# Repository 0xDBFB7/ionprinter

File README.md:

```
    _                       __        _  __   __  
   (_)____   ____   ____   / /____   (_)/ /_ / /_ 
  / // __ \ / __ \ / __ \ / // __ \ / // __// __ \
 / // /_/ // / / // /_/ // // /_/ // // /_ / / / /
/_/ \____//_/ /_/ \____//_/ \____//_/ \__//_/ /_/ 
```                                        

# Ionolith

Hardware, firmware, software, and documentation for ion printers.

This was an extremely speculative (and arguably pseudoscientific) project to attempt to scale up physical vapor deposition beyond all reasonable limits. I got as far as building a high vacuum chamber, testing a few "bowtie" crucible designs, etc.

Spinoffs:

- a GPU-accelerated Particle-In-Cell program called [Nyion](https://github.com/0xDBFB7/Nyion) 
- A cheap silicon carbide [furnace](https://0xdbfb7.com/furnace.html)
- A cheap controller for Varian Turbo-V200 series of pumps [varian-turbo-controller](https://github.com/0xDBFB7/varian-turbo-controller)
- Control software for an Inficon BPG-400 vacuum gauge [gauge.py](https://gist.github.com/0xDBFB7/7bd7048c6639270e6f291a2673903184)

This whole project was far beyond my capabilities, suffers from a lack of basic physical modelling in the beam region, and so there is little basis to expect this to work.

At the time the project was suspended, it looked something like this:

The ultimate goal was to produce an ultra high current (somewhere around 100 A of ionized aluminum accelerated to 100 to 1000 eV) heavy ion beam deposition system, aiming to 3D print large parts at cubic centimeters per hour and with arbitrary combinations of alloys and crystalline structure. 

  - Heavy ions like Al move slowly, meaning space charge effects are huge and, due to so-called "beam rigidity", magnetic focusing is useless.
  - However, this was developed under the (as yet untested assumption) that it would be possible to use a sort of active space-charge neutralization, actively injecting and confining electrons into metal-ion "packets" in the beam, to neutralize the beam space charge (something like [Gotoh 2012]).
  - Spreading the beam current over 512 or 1024 individually-controlled emitters in a 0.25 m^2 area seemed like it might alleviate deposition surface roughness issues, because of the wide range of angles of incidence.(See [Yang and Zhou, 1999, 2001])
  - Feedstock would be vaporized in "bowtie" structure - perhaps graphite-loaded magnesium oxide, perhaps coated in aluminum nitride, and with layers of ceramic multi-layer insulation to mitigate heat loss. Basic testing on a graphite bowtie was done.
  - Design goal of <$2000 cost, ideally run from a single 1500w outlet, with integrated diffusion pump.
  - Acceleration voltages over ~5000 V would pose huge X-ray and general power consumption (dozens of kilowatts in the beam!) and deposition power density (build platform overheating) issues.

```
Gotoh Y, Tsuji H, Taguchi S, Ikeda K, Kitagawa T, Ishikawa J, et al. Neutralization of space charge on high-current low-energy ion beam by low-energy electrons supplied from silicon based field emitter arrays. AIP Conference Proceedings, vol. 1496, 2012, p. 368–71.
Zhou XW, Wadley HNG. Hyperthermal vapor deposition of copper: reflection and resputtering effects. Surface Science 1999;431:58–73. https://doi.org/10.1016/S0039-6028(99)00336-2.
Yang YG, Zhou XW, Johnson RA, Wadley HNG. Monte Carlo simulation of hyperthermal physical vapor deposition. Acta Materialia 2001;49:3321–32. https://doi.org/10.1016/S1359-6454(01)00139-2.
```

For all references involved, see the file references.bib.

# <3     

# :D

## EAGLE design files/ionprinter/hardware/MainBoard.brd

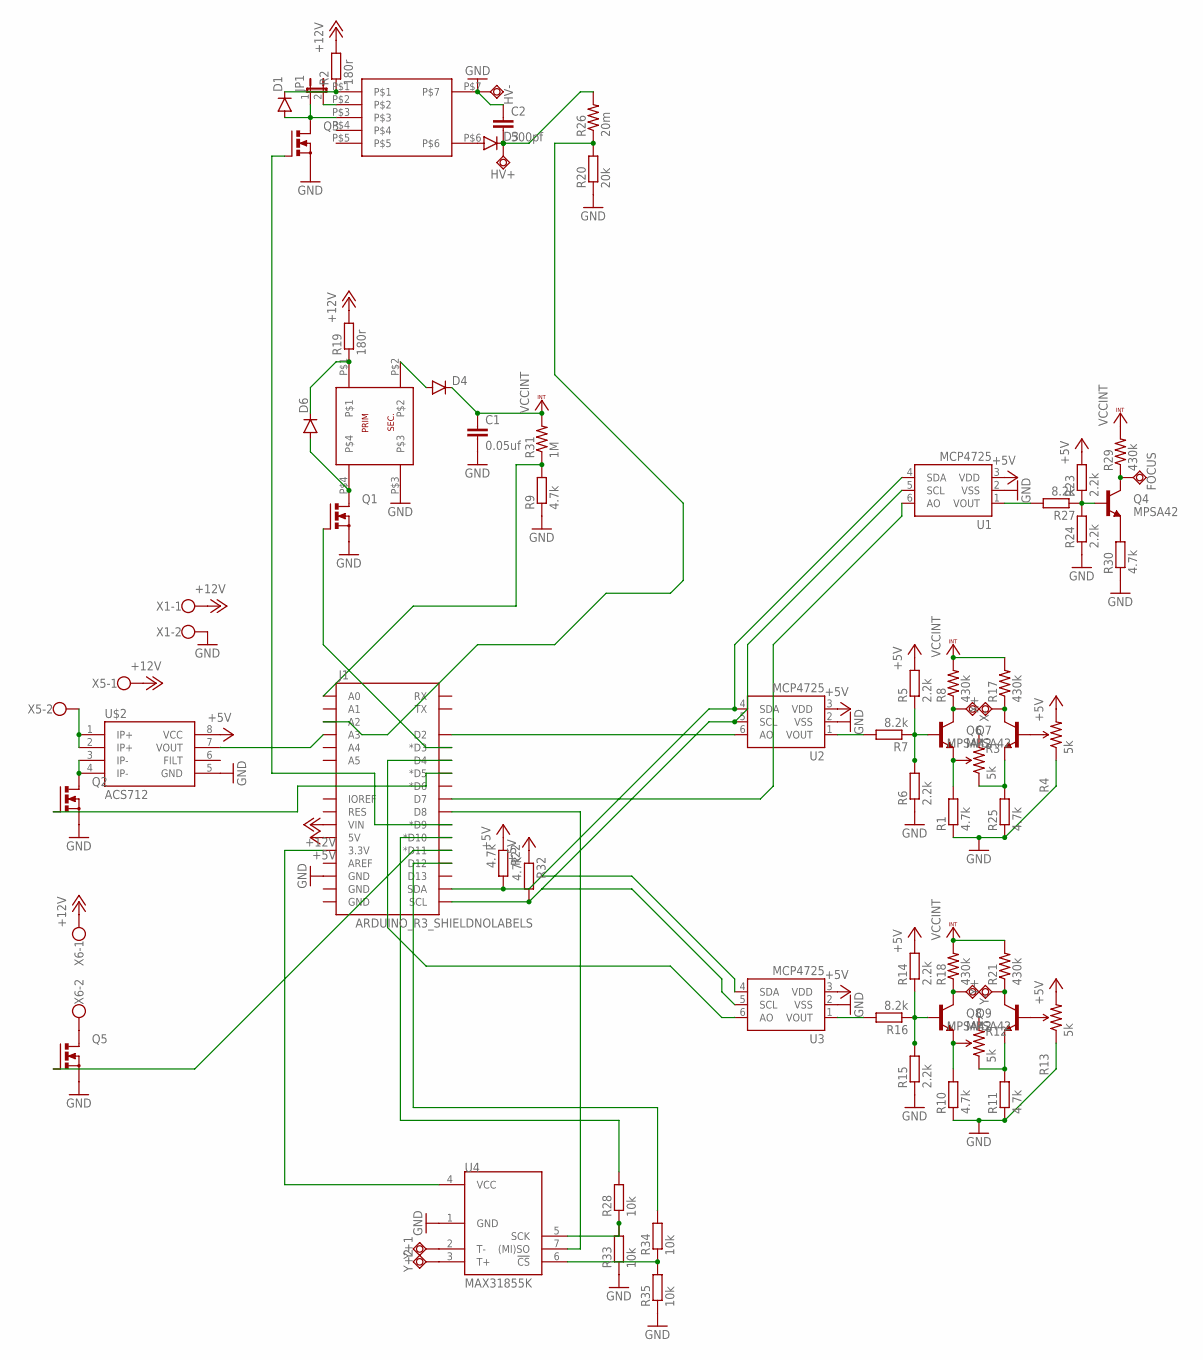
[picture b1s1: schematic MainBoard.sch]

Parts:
C1: 0.05uf; C1206
C2: 500pf; C1206
D1, D4, D6: DIODESOD123; SOD-123
D3: DIODEPTH; DIODE-1N4001
FOCUS: FOCUS; P1-13
HV+: TPSQPAD1-13; P1-13
HV-: TPSQPAD1-13; P1-13
J1: ARDUINO_R3_SHIELDNOLABELS; UNO_R3_SHIELD_NOLABELS
JP1: JUMPER-2SMD-NO; SJ_2S-NO
Q1, Q2, Q3, Q5: N-MOSFET-SO8S; SO-08
Q4, Q6, Q7, Q8, Q9: MPSA42; SOT23-3
R1, R9, R10, R11, R22, R25, R30, R32: 4.7k; R0603
R2, R19: 180r; R0603
R3, R4, R12, R13: 5k; TRIMPOT_PTH_S3_LOCK
R5, R6, R14, R15, R23, R24: 2.2k; R0603
R7, R16, R27: 8.2k; R0603
R8, R17, R18, R21, R29: 430k; 1206
R20: 20k; R0603
R26: 20m; AXIAL-0.4
R28, R33, R34, R35: 10k; R0603
R31: 1M; 1206
U1, U2, U3: MCP4725; SOT23-6
U4: MAX31855K; SOIC8
U$1: ATB; ATB3225
U$2: ACS712; SO08
U$3: CTX
X1, X5, X6: W237-102
X+: TPSQPAD1-13; P1-13
X-: TPSQPAD1-13; P1-13
Y+, Y+1, Y+2: TPSQPAD1-13; P1-13
Y-: TPSQPAD1-13; P1-13

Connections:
+5V: J1.5V, R4.3 (CW), R5.2, R13.3 (CW), R14.2, R22.1, R23.2, R32.1, U1.3 (VDD), U2.3 (VDD), U3.3 (VDD), U$2.8 (VCC)
+12V: J1.VIN, R2.2, R19.2, X1.1, X5.1, X6.1
GND: C1.2, C2.1, HV-.TP, J1.GND@2 (GND), Q1.1 (S), Q1.2 (S), Q1.3 (S), Q2.1 (S), Q2.2 (S), Q2.3 (S), Q3.1 (S), Q3.2 (S), Q3.3 (S), Q5.1 (S), Q5.2 (S), Q5.3 (S), R1.1, R4.1 (CCW), R6.1, R9.1, R10.1, R11.1, R13.1 (CCW), R15.1, R20.1, R24.1, R25.1, R30.1, R33.1, R35.1, U1.2 (VSS), U2.2 (VSS), U3.2 (VSS), U4.1 (GND), U$1.P$3, U$2.5 (GND), U$3.P$7, X1.2
unnamed: Q6.3 (C), R8.1, X-.TP
unnamed: Q7.3 (C), R17.1, X+.TP
unnamed: R7.2, U2.1 (VOUT)
unnamed: Q6.2 (E), R1.2, R3.2 (WIPER)
unnamed: Q7.2 (E), R3.1 (CCW), R25.2
unnamed: Q7.1 (B), R4.2 (WIPER)
unnamed: Q9.1 (B), R13.2 (WIPER)
unnamed: Q6.1 (B), R5.1, R6.2, R7.1
unnamed: Q4.2 (E), R30.2
unnamed: J1.D3 (*D3), Q1.4 (G)
unnamed: Q8.2 (E), R10.2, R12.2 (WIPER)
unnamed: Q9.2 (E), R11.2, R12.1 (CCW)
unnamed: J1.SDA, R22.2, U1.4 (SDA), U2.4 (SDA), U3.4 (SDA)
unnamed: Q8.1 (B), R14.1, R15.2, R16.1
unnamed: Q9.3 (C), R21.1, Y+.TP
unnamed: Q8.3 (C), R18.1, Y-.TP
unnamed: R16.2, U3.1 (VOUT)
unnamed: J1.D2, U2.6 (AO)
unnamed: J1.D4, U3.6 (AO)
unnamed: J1.A0, R9.2, R31.1
unnamed: D6.A, Q1.5 (D), Q1.6 (D), Q1.7 (D), Q1.8 (D), U$1.P$4
unnamed: D4.A, U$1.P$2
unnamed: Q2.5 (D), Q2.6 (D), Q2.7 (D), Q2.8 (D), U$2.3 (IP-), U$2.4 (IP-)
unnamed: U$2.1 (IP+), U$2.2 (IP+), X5.2
unnamed: J1.D5 (*D5), Q2.4 (G)
unnamed: D1.A, JP1.1, Q3.5 (D), Q3.6 (D), Q3.7 (D), Q3.8 (D), U$3.P$3
unnamed: JP1.2, U$3.P$2
unnamed: D1.C, R2.1, U$3.P$1
unnamed: D3.A, U$3.P$6
unnamed: C2.2, D3.C, HV+.TP, R26.P$2 (2)
unnamed: R28.1, R33.2, U4.5 (SCK)
unnamed: D6.C, R19.1, U$1.P$1
unnamed: Q4.1 (B), R23.1, R24.2, R27.1
unnamed: R27.2, U1.1 (VOUT)
unnamed: J1.SCL, R32.2, U1.5 (SCL), U2.5 (SCL), U3.5 (SCL)
unnamed: FOCUS.TP, Q4.3 (C), R29.1
unnamed: R34.1, R35.2, U4.6 (!CS)
unnamed: J1.D9 (*D9), Q3.4 (G)
unnamed: J1.D10 (*D10), R28.2
unnamed: J1.A2, R20.2, R26.P$1 (1)
unnamed: Q5.5 (D), Q5.6 (D), Q5.7 (D), Q5.8 (D), X6.2
unnamed: J1.D11 (*D11), Q5.4 (G)
unnamed: J1.A3, U$2.7 (VOUT)
unnamed: J1.D12, R34.2
unnamed: J1.D7, U1.6 (AO)
unnamed: J1.D8, U4.7 ((MI)SO)
unnamed: U4.2 (T-), Y+1.TP
unnamed: U4.3 (T+), Y+2.TP
unnamed: J1.3.3V, U4.4 (VCC)
VCCINT: C1.1, D4.C, R8.2, R17.2, R18.2, R21.2, R29.2, R31.2

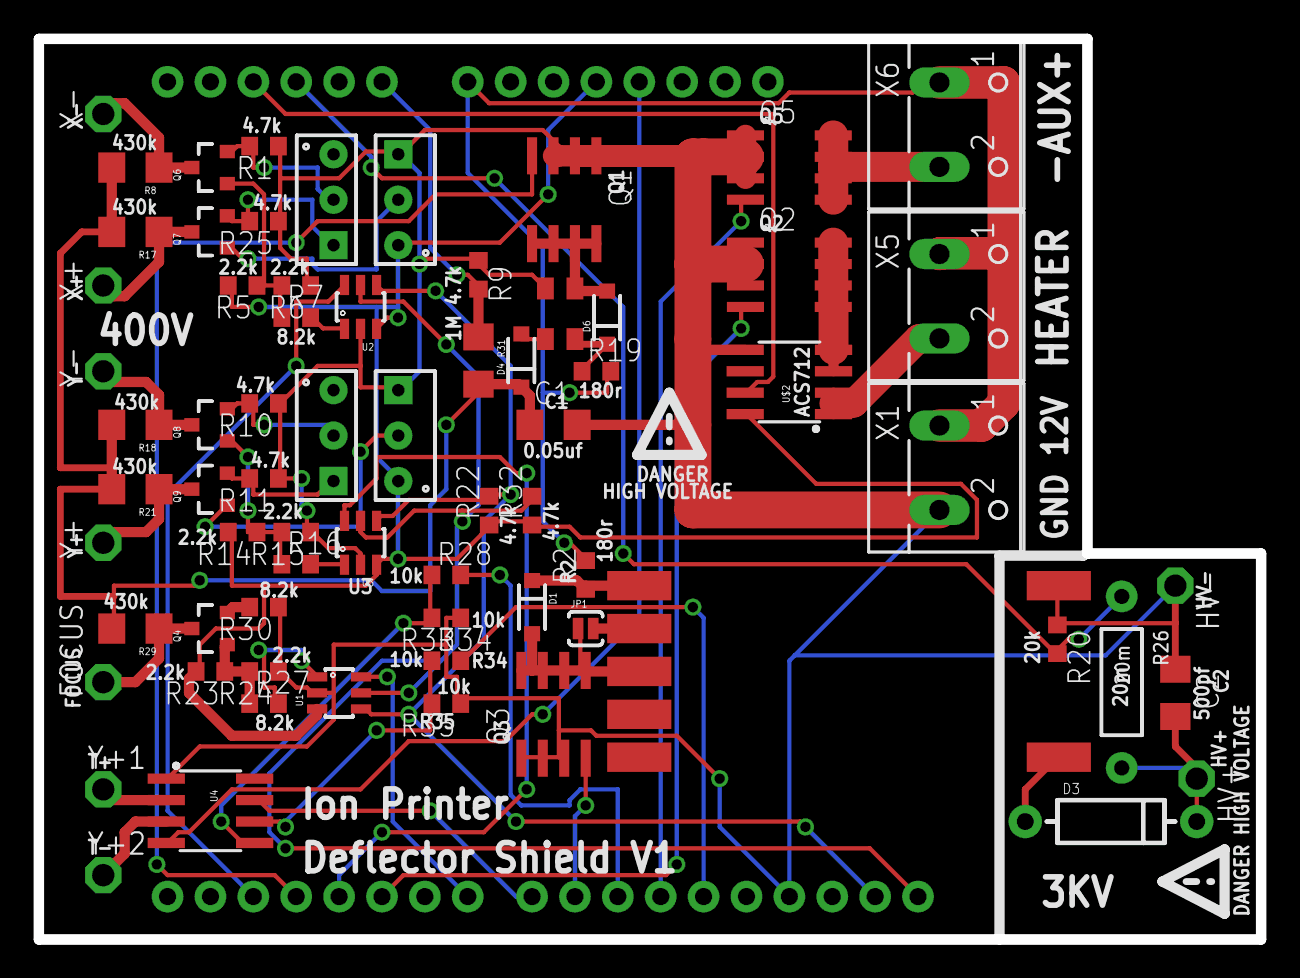
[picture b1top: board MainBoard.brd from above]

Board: 2 copper layers, 72.4 x 53.3 mm, 71 parts (0 on the bottom side), 53 nets.

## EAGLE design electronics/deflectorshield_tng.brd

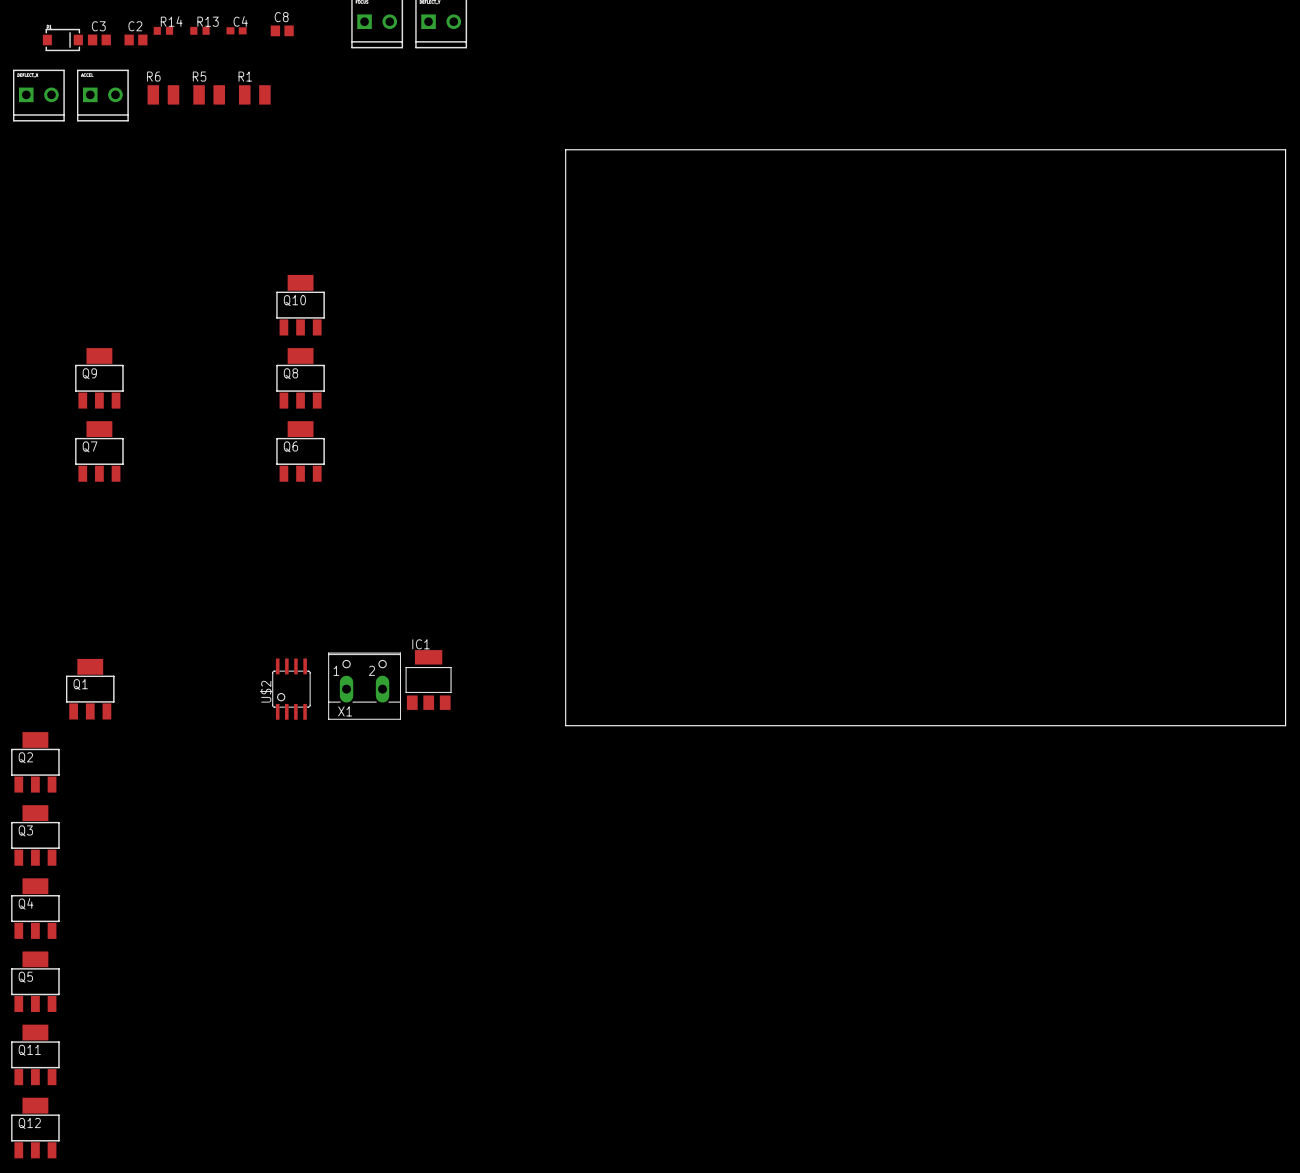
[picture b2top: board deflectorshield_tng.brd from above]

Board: 2 copper layers, 100.0 x 80.0 mm, 29 parts (0 on the bottom side), 14 nets, no tracks yet.

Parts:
ACCEL: SCREWTERMINAL-3.5MM-2
C2, C3: C0805
C4: 0.1uf; C0603
C8: 10uf; C0805
D1: SMA-DIODE
DEFLECT_X: SCREWTERMINAL-3.5MM-2
DEFLECT_Y: SCREWTERMINAL-3.5MM-2
FOCUS: SCREWTERMINAL-3.5MM-2
IC1: REG1117; SOT223
Q1, Q6, Q7, Q8: N-HEXFET_SOT323-IRLL2705; SOT223
Q2, Q3, Q4, Q5, Q9, Q10, Q11, Q12: SOT223
R1, R5, R6: 2.2r; R1210
R13, R14: 1k; R0603
U$2: LM5109; SOIC8
X1: W237-102

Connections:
12V: C8.1, R1.1, U$2.1
A_HI: R13.2, U$2.2
A_LO: R14.2, U$2.3
GND: C8.2, IC1.1, Q6.3, R13.1, R14.1, U$2.4
unnamed: DEFLECT_X.2, Q2.3, Q3.4
unnamed: Q4.3, Q5.4
unnamed: Q11.3, Q12.4
unnamed: Q7.3, Q8.4
unnamed: D1.A, R1.2
unnamed: C4.1, D1.C, U$2.8
unnamed: C4.2, U$2.6
unnamed: DEFLECT_X.1, Q9.3, Q10.4
unnamed: R5.1, U$2.7
unnamed: R6.1, U$2.5

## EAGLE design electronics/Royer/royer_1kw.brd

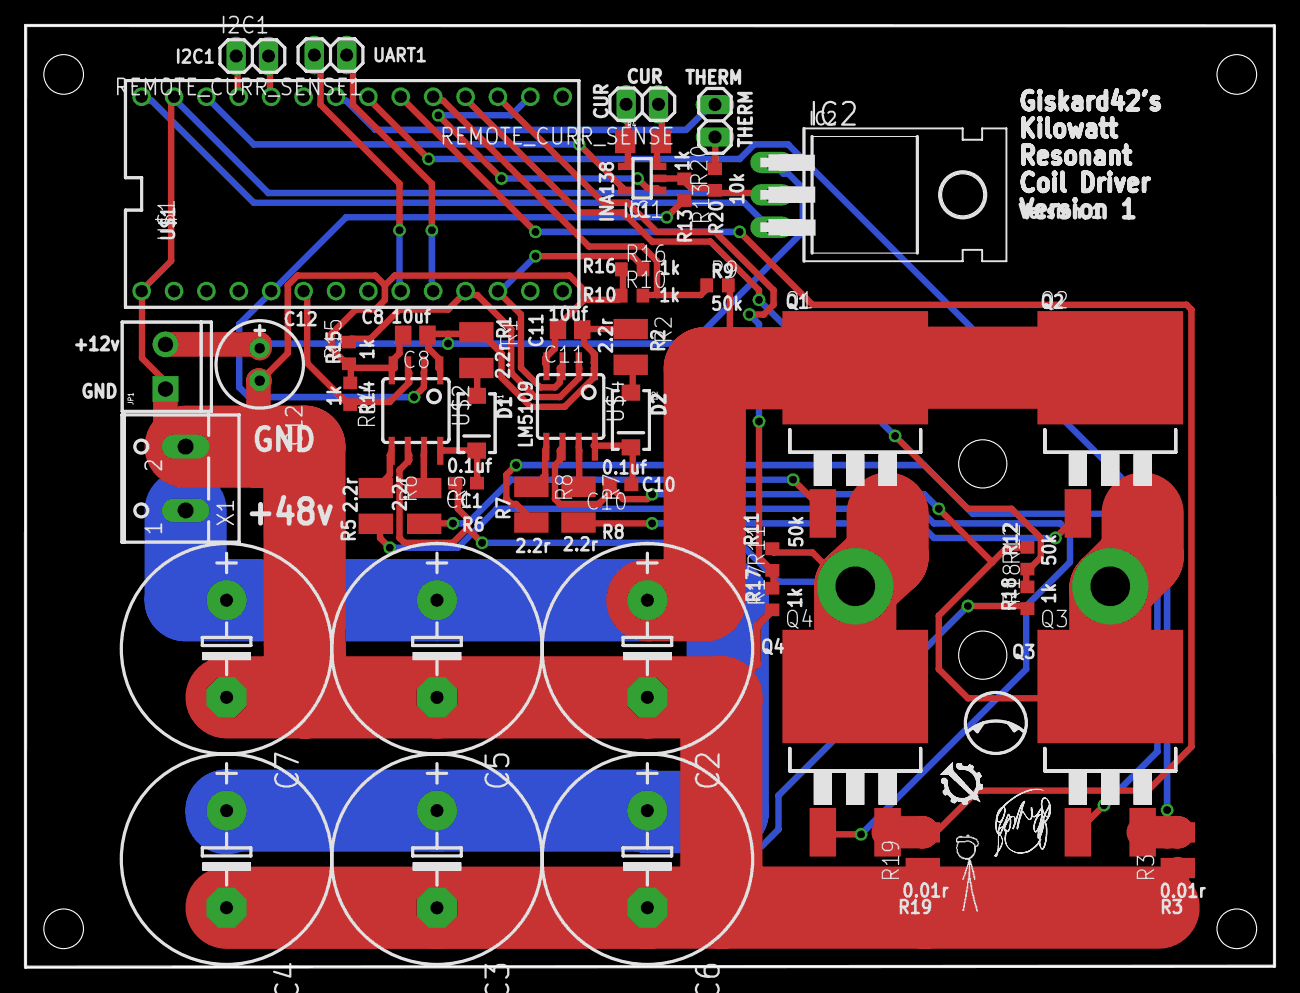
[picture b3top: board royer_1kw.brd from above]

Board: 2 copper layers, 97.9 x 73.8 mm, 48 parts (0 on the bottom side), 37 nets.

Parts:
C1, C10: 0.1uf; C0603
C2, C3, C4, C5, C6, C7: E7,5-16
C8, C11: 10uf; C0805
C12: E2,5-7
D1, D2: SMA-DIODE
I2C1: UART1; 1X02
IC1: INA138; SOT23-5
IC2: 7805T; TO220H
JP1: SCREWTERMINAL-3.5MM-2
Q1, Q2, Q3, Q4: IRF3704S; D2PACK
R1, R2, R5, R6, R7, R8: 2.2r; R1210
R3, R19: 0.01r; R3225
R4: 1206
R9, R11, R12: 50k; R0603
R10, R13, R14, R15, R16, R17, R18: 1k; R0603
R20: 10k; R0603
REMOTE_CURR_SENSE: 1X02
REMOTE_CURR_SENSE1: UART1; 1X02
THERMISTOR: 1X02
U$1: TEENSY_LC_DIL; TEENSY_3.0-3.2&LC_DIL
U$2, U$4: LM5109; SOIC8
X1: W237-102

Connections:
3V3: IC1.5, U$1.3.3V
5V: IC2.3, U$1.VIN
12V: C8.1, C11.1, C12.+, IC2.1, JP1.2, R1.1, R2.1, U$2.1, U$4.1
48V: C2.+, C3.+, C4.+, C5.+, C6.+, C7.+, Q1.2, Q2.2, R9.2, X1.1
48V_SENSE: R9.1, R10.2, U$1.17/A3
A_HI: R13.2, U$1.3, U$2.2
A_LO: R14.2, U$1.4, U$2.3
A_PHASE: C1.2, Q1.3, Q4.2, R11.2, U$2.6
A_PHASE_CURRENT: Q4.3, R19.2, U$1.18/A4
A_PHASE_V: R11.1, R17.2, U$1.15/A1
B_HI: R15.2, U$1.9, U$4.2
B_LO: R16.2, U$1.10, U$4.3
B_PHASE: C10.2, Q2.3, Q3.2, R12.2, U$4.6
B_PHASE_CURRENT: Q3.3, R3.2, U$1.19/A5
B_PHASE_V: R12.1, R18.2, U$1.16/A2
GND: C2.-, C3.-, C4.-, C5.-, C6.-, C7.-, C8.2, C11.2, C12.-, IC1.2, IC2.2, JP1.1, R3.1, R10.1, R13.1, R14.1, R15.1, R16.1, R17.1, R18.1, R19.1, R20.1, U$1.AGND, U$1.GND, U$2.4, U$4.4, X1.2
unnamed: R7.1, U$4.7
unnamed: R8.1, U$4.5
unnamed: Q1.1, R5.2
unnamed: Q4.1, R6.2
unnamed: D1.A, R1.2
unnamed: C1.1, D1.C, U$2.8
unnamed: IC1.3, R4.2, REMOTE_CURR_SENSE.1
unnamed: Q2.1, R7.2
unnamed: Q3.1, R8.2
unnamed: D2.A, R2.2
unnamed: C10.1, D2.C, U$4.8
unnamed: IC1.4, R4.1, REMOTE_CURR_SENSE.2
unnamed: R20.2, THERMISTOR.2
unnamed: R5.1, U$2.7
unnamed: R6.1, U$2.5
unnamed: REMOTE_CURR_SENSE1.1, U$1.8
unnamed: REMOTE_CURR_SENSE1.2, U$1.7
unnamed: I2C1.1, U$1.23/A9
unnamed: I2C1.2, U$1.22/A8
REMOTE_CURR_SENSE: IC1.1, U$1.14/A0
THERM: THERMISTOR.1, U$1.20/A6

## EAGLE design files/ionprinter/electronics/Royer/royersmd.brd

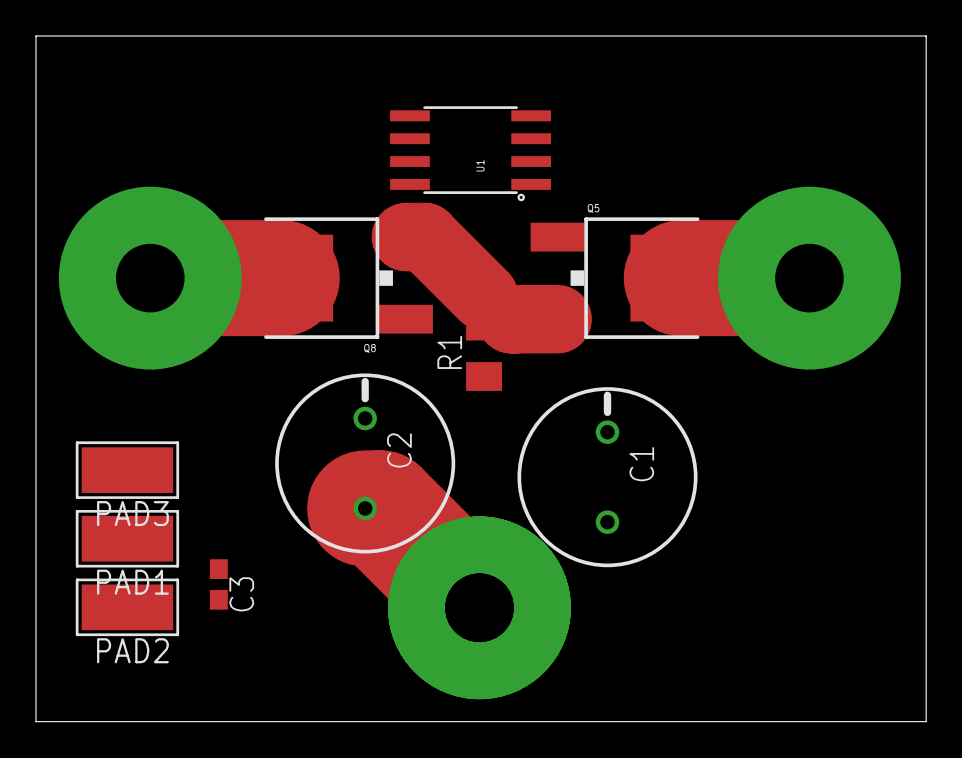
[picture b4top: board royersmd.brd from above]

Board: 2 copper layers, 49.5 x 38.1 mm, 10 parts (0 on the bottom side), 8 nets.

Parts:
C1, C2: SANYO-OSCON_9F
C3: 0.1uf; C0603
PAD1, PAD2, PAD3: WIREPADSMD5-2,5; 5-2,5
Q5, Q8: MOSFET-NCHANNELFDD8780; DPAK
R1: M1206
U1: Tiny45-20-SMT; SO08-EIAJ

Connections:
48V: C1.+, C2.+
GATE_1: Q8.1, U1.5
GATE_2: Q5.1, U1.6
GATE_SENSE_1: Q5.3, Q8.3, R1.2, U1.2
GND: C1.-, C2.-, R1.1
unnamed: PAD3.1, U1.7
unnamed: C3.1, PAD1.1, U1.8
unnamed: C3.2, PAD2.1, U1.4

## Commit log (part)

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2019-04-22 Sim fully functional, but no true solutions have yet presented themselve
2019-04-22 Maybe trying DEAP?
2019-04-22 building?
2019-04-24 Experiments!
2019-04-24 The .sif files got overwritten somehow
2019-04-25 Bowtie sim working again
2019-04-26 C++ poisson solver working
2019-04-26 Oh lovely, convergence!
2019-04-26 Doesn't work if more grid points are specified
2019-04-27 Heavy beam also mostly functional
2019-04-29 some experiments
2019-05-01 Some additional theory
2019-05-01 Reflector testing
2019-05-01 More theory, beam diagnostics
2019-05-03 Some nonsense
2019-05-05 Updated graphite resistivity value
2019-05-06 irritated at simulations.
2019-05-06 Working on multiphysics sim
2019-05-07 Using VTK for solid import
2019-05-08 More work on multiphysics
2019-05-11 Adding unit testing to multiphysics
2019-05-11 Unit testing's working!
2019-05-12 oh man
2019-05-12 removed douchebag
2019-05-14 Unit testing and new kiln
2019-05-14 PID furnace
2019-05-15 haha fuck!
2019-05-15 stupid
2019-05-18 aww yis! Ceramics!
2019-05-25 Ceramics improvements
2019-05-28 Trianglar insulators
2019-05-28 Rectangular insulators!
2019-05-29 Switching test frameworks
2019-05-29 directory structure's a little convoluted, wish I didn't need cmake
2019-05-29 Catch2 compiles waaay too slowly
2019-05-30 renamed multiphysics to nyion because whimsicality
2019-05-31 Multiphysics!
2019-06-01 VTU export
2019-06-01 haha, mental health.
2019-06-02 Work on relaxation
2019-06-03 Gauss-seidel working
2019-06-03 Adding mesh refinement
2019-06-04 Charge density!
2019-06-08 haha! Gotcha
2019-06-08 Data!
2019-06-08 More timing data!
2019-06-08 Haha! All the versatility and safety of std::vectors!
2019-06-09 Quite fast - 400 ms with cache alignment
2019-06-09 MPI!
2019-06-09 112.8 ms single core!
2019-06-09 Frighteningly fast.
2019-06-09 fuck, what a waste of time
2019-06-13 moving on
2019-06-14 Adding multigrid
2019-06-14 Perhaps a more orthodox "tree" structure would be better
2019-06-15 dAtA sTRucTuRes!
2019-06-16 actually quite respectable times - 640 ms per cycle
2019-06-16 damn, 1 second per cycle
2019-06-16 Laplace functional again
2019-06-17 coarsen is a FUCKER
2019-06-17 SOR doesn't do much
2019-06-17 getting some intense Multigrid action right here
2019-06-17 SOR helps a little now
2019-06-17 Trying FPGA acceleration
2019-06-18 Trying to optimize the relax loop
2019-06-18 oh hell yeah that's fast
2019-06-18 some strange convergence glitches
2019-06-18 putting std_vectors at the interface
2019-06-18 changing data structure yet again
2019-06-19 something strange with uninitialized memory
2019-06-19 fixed broken laplace
2019-06-19 fixing a few scale issues
2019-06-19 I must've screwed something up in the unrolled section
2019-06-19 gotcha
2019-06-19 Laplace working well
2019-06-20 Still not fast enough, let's do conjugate gradient.
2019-06-21 Something seriously wrong with the solver
2019-06-21 solver certainly seems to be working fine now
2019-06-21 guess I'll need conjugate gradient
2019-06-21 trying out floats for a sec
2019-06-22 A definite improvement
2019-06-22 trying v-cycle again
2019-06-22 holy shit! convergence of 29!
2019-06-26 Multigrid still not functional
2019-06-26 Let's tidy this thing up.
2019-06-29 fuck
2019-07-03 More unit testing!
2019-07-03 Unit testing is the best!
2019-07-03 Oh gosh is it ever! I love this style of development!
2019-07-03 Further bug fixes
2019-07-03 Stencil function thoroughly unit tested.
2019-07-05 Relative lookup is far too slow
2019-07-05 Tripped up by copy-by-value
2019-07-06 refinement functional
2019-07-06 Multigrid: it works.
2019-07-07 trying something crazy
2019-07-09 Opengl!
2019-07-10 OpenGL keyboard navigation
2019-07-14 Mesh visualization
2019-07-17 nonsense or whatever
2019-07-17 MCVE of 2d/3d swap working
2019-07-17 Still working...
2019-07-17 OpenGL fully refactored
2019-07-17 this that and the other
2019-07-19 Multiple windows functioning properly
2019-07-19 Graphing!
2019-07-19 Proper mesh coloring
2019-07-20 Fixed min/max functions
2019-07-21 Fixed compiler warnings
2019-07-22 Found the problem
2019-07-23 Stencils functional
2019-07-27 Fixed relative lookup once again
2019-07-27 homogenization complete
2019-07-29 done
2019-08-01 refactored relative indexing yet again
2019-08-01 Refactoring a bunch, not sure how it'll work out
2019-08-10 fpga
2019-08-10 what
2019-08-11 bunch o' dumb playing around
2019-08-11 opencl boilerplate
2019-08-12 can't take my eyes off you
2019-08-13 Tossing almost everything out in favor of simple rectangular mesh
2019-08-13 More munging
2019-08-13 death to code!
2019-08-14 If you're having kernel problems I feel bad for you son
    I got 99 p. but a kernel aint one
2019-08-14 Global classes
2019-08-15 Unit tests
2019-08-15 Improved gauss-seidel using OpenCL's cool NDRange thang
2019-08-15 Array initialization is important!
2019-08-16 Almost got restriction
2019-08-17 Faster restriction, still borked though
2019-08-17 Restriction's actually working fine
2019-08-17 Further benchmarking
2019-08-18 Residual abandoned
2019-08-20 Switching to unigrid
2019-08-20 Unigrid g-s working
2019-08-20 Unigrid g-s actually working
2019-08-21 Unigrid g-s actually actually working
2019-08-21 Trimmed fat, linterp too slow
2019-08-21 Thought perhaps double buffering would improve linterp, it didn't
2019-08-21 Aha, performance now much improved
2019-08-22 Linterp definitely working properly.
2019-08-22 Everything's working?
2019-08-23 Let's do this by the book.
2019-08-24 G-S Python test
2019-08-24 Figured out the issue
2019-08-25 Working!
2019-08-26 Even better convergence
2019-08-27 3d Python implementation.
2019-08-27 Comparing functions
2019-08-27 Concurrency issues with gauss-seidel.
2019-08-27 Yay!
2019-08-27 Hybrid g-s scheme
2019-08-28 FMG cycle
2019-08-28 Fixed boundary bug
2019-08-29 still failure
2019-08-30 Figuring a few things out
2019-08-30 Possibly set up correctly?
2019-08-31 Somehow test10 works.
2019-08-31 Residual correction mostly working?
2019-08-31 Borrowing Dr. Malpeddi's implementation
2019-09-01 Reworking slightly, trying to add BCs
2019-09-01 damn, I broke it
2019-09-02 Better still
2019-09-02 Something
2019-09-03 Almost converging...
2019-09-03 Converges quite steadily
2019-09-03 Yay! it works!
2019-09-03 Gosh darnit, a sneaky exponential function!
2019-09-03 Damped jacobi and full unigrid
2019-09-03 At attempt at weighted restrict
2019-09-03 An attempt at extended boundaries
2019-09-03 test
2019-09-04 Optimization
2019-09-04 Implementing in OpenCL
2019-09-05 OpenCL multigrid, still too slow
2019-09-05 GPU optimizing
2019-09-05 Splitting unigrid into compute/apply
2019-09-10 Figuring out why jacobi is so much faster than corrections
2019-09-10 Fixed float type issue
2019-09-19 Ceramics 2
2019-09-23 dissemination
2019-09-25 Taalk
2019-09-28 philosophy
2019-10-01 Misunderstood preconditioning
2019-10-05 Bastardized now has standard convergence behavior
2019-10-05 Higher-order stencils work great
2019-10-05 More higher-order stencils
2019-10-05 Multigrid
2019-10-16 dumb
2019-10-16 More words
2019-10-19 Multilayer insulation looks promising
2019-10-19 Progress on refinement scheme
2019-10-21 More progress on refinement
2019-10-27 Still working on data structure
2019-10-29 MLI furnace print
2019-11-05 Not much progress
2019-11-05 Committing before re-organizing
2019-11-06 Data structure is breaking my brain, so graphviz to the rescue
2019-11-06 Data structure
2019-11-07 Several hours of graphviz later,
2019-11-09 Non-recursive traverse working
2019-11-14 Sync_ghosts working
2019-11-30 Depression's lifting! I can do this! Inlined code!
2019-12-03 Math in OpenMP offload, more words
2019-12-04 A few more benchmark tests with OpenMP
2019-12-16 Annoyed with elmer
2019-12-25 Cmaking out
2019-12-25 CMake build working
2019-12-26 Cmake test build working too
2019-12-28 Removed hideous gotos
2019-12-29 jeez, cpputest and ROOT don't seem to get along
2019-12-29 Removing root in favour of mathgl
2019-12-29 Root removed
2019-12-30 Visualize mostly working
2019-12-30 Test ignoring.
2019-12-30 Re-organized directory structure for SSD
2019-12-31 Named pretty printer.
2019-12-31 vvv pretty preprocessor
2020-01-02 More nyion
2020-01-02 Great progress!
2020-01-03 Scales functional
2020-01-04 Array helper progressing
2020-01-05 Oh gosh! first real visuals - and it's pretty!
2020-01-05 Getting excited and not testing - code suffering as a result. Must test more comprehensively.
2020-01-05 Hot air
2020-01-05 Graphs!
2020-01-05 Bug squashed! State is jumping around a bit more than I'd prefer, but oh well.
2020-01-05 More unit testing
2020-01-06 Fighting unit testing software
2020-01-06 Benchmarking, optimizing, inlining
2020-01-06 Words
2020-01-10 Cuda still isn't running.
2020-01-10 Got it!
2020-01-10 Fixed ASAN issue
2020-01-10 Simplified CMAKE
2020-01-11 Improved compile speeds
2020-01-11 Re-organizing
2020-01-11 Fixed build
2020-01-11 Fixed cell_world_lookup
2020-01-24 Google Test
2020-01-29 This whole thing is dumb and stupid.
2020-01-31 Goddamn thing
2020-02-02 FLTK included and functional, some misgivings
2020-02-06 Logging of console
2020-02-08 class functions work? Huh, cool.
2020-02-08 Cleaning up mesh representation
2020-02-09 Phys_mesh structure in
2020-02-09 OOPifying slightly
2020-02-09 Not an ideal structure.
2020-02-10 Adding tests for structure
2020-02-10 Simplifying traverse
2020-02-16 No progress
2020-02-16 Debug improvements
2020-02-18 Tried out mediawiki, not ideal
2020-02-19 Array_helper progress
2020-02-19 Fixed a few things on the device data structure side
2020-02-19 Data structure...
2020-02-19 Build broke
2020-02-19 got it.
2020-02-19 One slick interface!
2020-02-19 Going to remove state.x
2020-02-20 Okay, let's slow down a bit here.
2020-02-20 CUDA transfers
2020-02-20 Disabled asan, somehow works now?
2020-02-20 Asan's got issues, man
2020-02-20 Fixed memleak in GPU copy
2020-02-20 too mANY POINTERS
2020-02-20 More progress
2020-02-20 Seems to work
2020-02-20 Progress.
2020-02-20 Hell yeah!
2020-02-20 More simplification required...
2020-02-20 ... and destructor too!
2020-02-20 wait, why don't we just leave the arrays as-is?
2020-02-20 Munge successful!
2020-02-21 ...now everything's broken
2020-02-21 Gotcha.
2020-02-21 Bi-directional struct copying! Hell yeah.
2020-02-21 Leak check working
2020-02-21 Benchmarking
2020-02-21 How do we serialize these tests?
2020-02-21 Neat way of documenting code...
2020-02-21 Mulling over particle representation
2020-02-22 Trying out doc script
2020-02-22 Fixed macros on transfer operation
2020-02-23 Re-organizing slightly
2020-02-23 Build fixed.
2020-02-23 Boy, what a mess
2020-02-23 wtffff
2020-02-23 Yay! build's actually fixed now
2020-02-23 Serialization in progress
2020-02-24 Unrolled operations progress
2020-02-24 What in tarnation
2020-02-24 Added asan tripwire
2020-02-24 Unrolled array is now functional!
2020-02-24 It's beautiful!
2020-02-24 mesh_depth isn't required anymore, I don't think
2020-02-24 Removed confusing mesh_depth
2020-02-24 Can't call refine from kernel yet
2020-02-25 More gpu changes
2020-02-25 Build fixed
2020-02-25 Actually fixed the build.
2020-02-25 Strange bugs!
2020-02-25 Serialization
2020-02-25 Traverse borken
2020-02-26 Apparently fixed traverse bug?
2020-02-26 Actually fixed traverse bug
2020-02-26 ghost linkages tba
2020-02-28 Ghost linkage progress
2020-02-29 Ghost copies
2020-03-01 wtf linking again :(
2020-03-01 Something specific to d_t_t.cu is breaking the build.
2020-03-01 ???? fixed?
2020-03-01 Ghost update working! Now for transforms...
2020-03-01 Transform apparently working
2020-03-02 Ghost linkages working
2020-03-02 Device copy ghosts
2020-03-03 Functional
2020-03-04 Jacobi
2020-03-04 Block sizing
2020-03-04 Oh wait, a 100^3 block is ridiculous!
2020-03-04 Block sizing fixed
2020-03-05 Jacobi functional!
2020-03-05 Hit the exact same benchmarks! Yay!
2020-03-05 Going to re-organize again to fix header deps
2020-03-05 Double buffering take 1
2020-03-05 Apparently working?
2020-03-05 Passing again
2020-03-05 Physics!
2020-03-14 Zotero!
2020-03-29 Radiation sim
2020-03-30 Raytracer
2020-03-31 Mesh inside-outside
2021-06-14 Cleanups for resume
2021-06-14 Resume, readme cleanups
2021-06-14 Resume, split out nyion

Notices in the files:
parts and their libraries:
SparkFun-DiscreteSemi: Licensing: Creative Commons ShareAlike 4.0 International - https://creativecommons.org/licenses/by-sa/4.0
